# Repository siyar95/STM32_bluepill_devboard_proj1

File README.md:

# STM32 Dev Board – Project 1

This project is a custom **development board** designed around the **STM32F103C8T6** microcontroller.  
It includes the essential peripherals for firmware development and prototyping:

## 🔧 Features

- **STM32F103C8T6** ARM Cortex-M3 microcontroller
- **USB (Device/Power)**
- **UART** interface for serial communication
- **SWD (Single Wire Debug)** header for programming and debugging
- **Linear voltage regulator** for stable 3.3V power supply

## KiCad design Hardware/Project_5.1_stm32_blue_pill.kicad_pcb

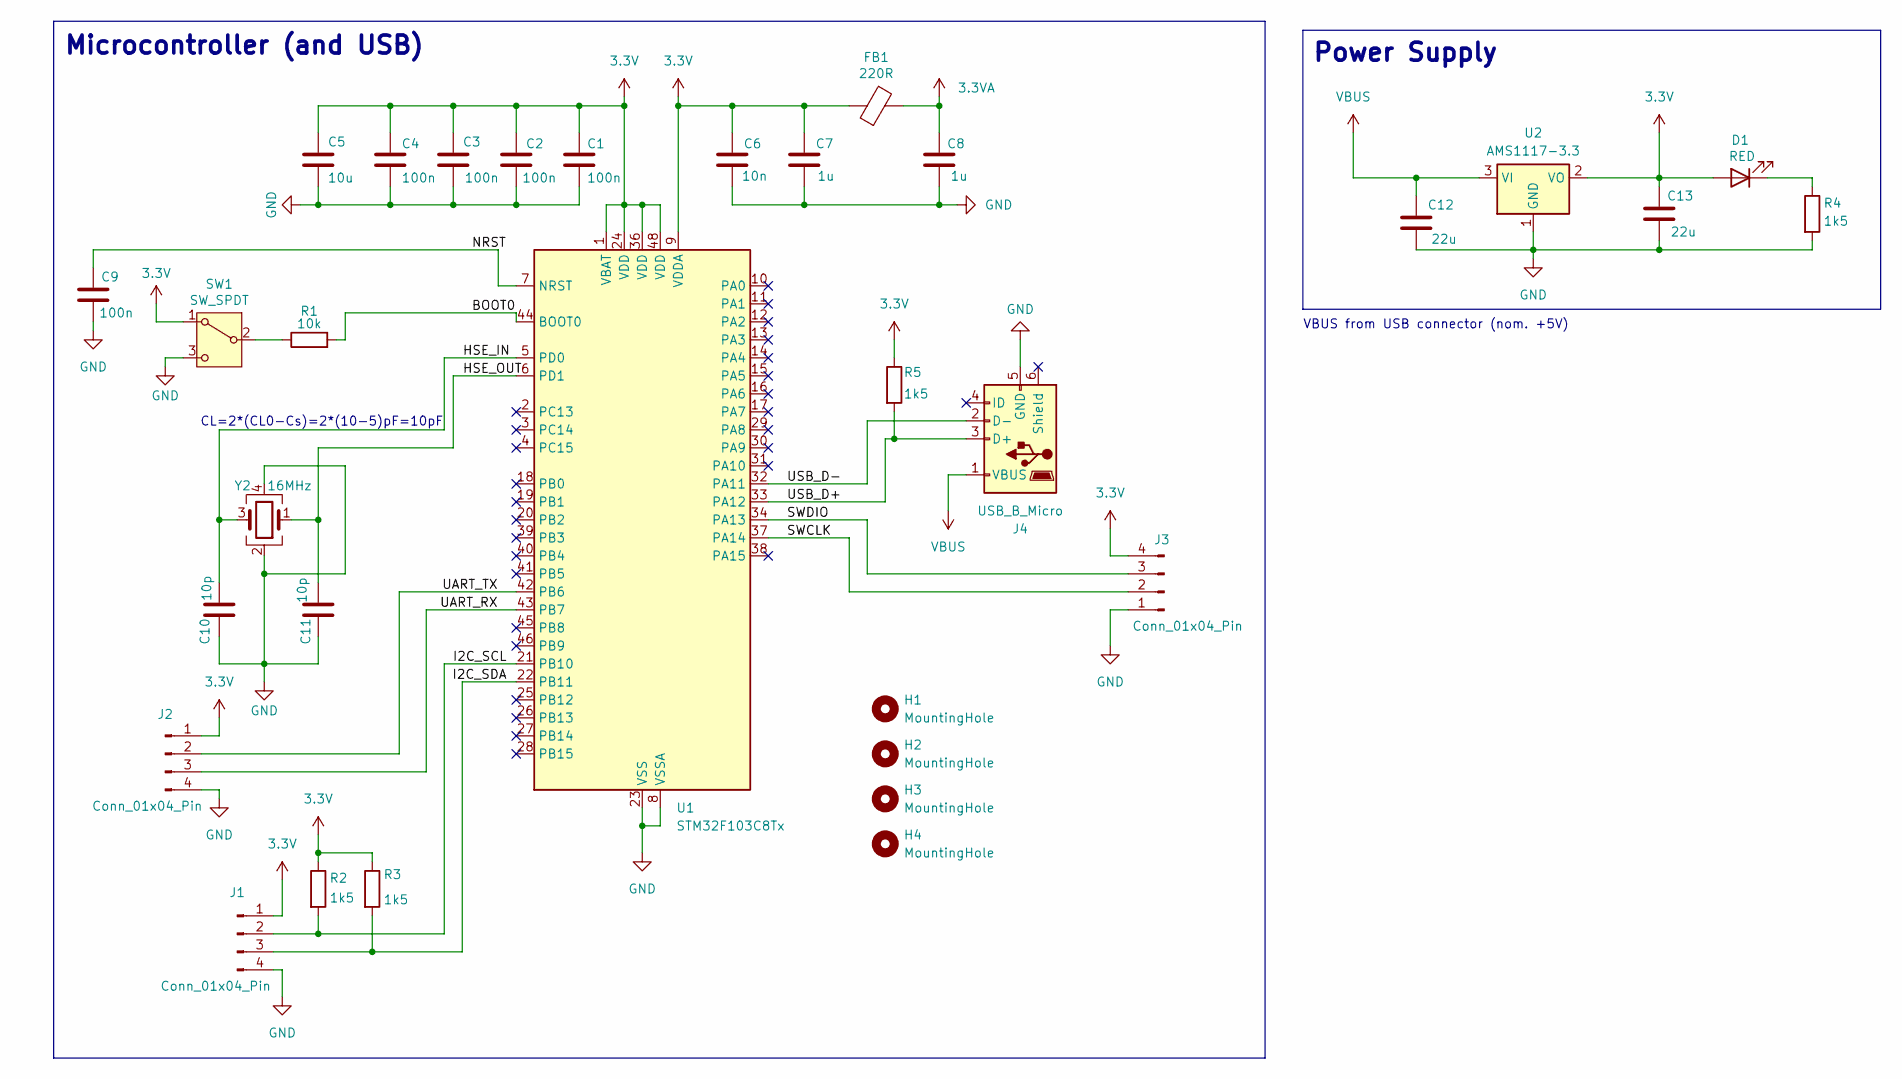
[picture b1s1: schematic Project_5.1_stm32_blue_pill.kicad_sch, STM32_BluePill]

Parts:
C1, C2, C3, C4, C9: 100n; C_0402_1005Metric
C5: 10u; C_0603_1608Metric
C6: 10n; C_0402_1005Metric
C7, C8: 1u; C_0402_1005Metric
C10, C11: 10p; C_0402_1005Metric
C12, C13: 22u; C_0805_2012Metric
D1: RED; LED_0603_1608Metric
FB1: 220R; L_0603_1608Metric
H1, H2, H3, H4: MountingHole; MountingHole_2.2mm_M2
J1, J2, J3: Conn_01x04_Pin; PinHeader_1x04_P2.54mm_Vertical
J4: USB_B_Micro; USB_Micro-B_Wuerth_629105150521
R1: 10k; R_0402_1005Metric
R2, R3, R4, R5: 1k5; R_0402_1005Metric
SW1: SW_SPDT; SW_SPDT_PCM12
U1: STM32F103C8Tx; LQFP-48_7x7mm_P0.5mm
U2: AMS1117-3.3; SOT-223-3_TabPin2
Y2: 16MHz; Crystal_SMD_Abracon_ABM8G-4Pin_3.2x2.5mm

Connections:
3.3V: C1.1, C2.1, C3.1, C4.1, C5.1, C6.1, C7.1, C13.1, D1.2 (A), FB1.1, J1.1, J2.1, J3.4, R2.1, R3.1, R5.1, SW1.1 (A), U1.1 (VBAT), U1.9 (VDDA), U1.24 (VDD), U1.36 (VDD), U1.48 (VDD), U2.2 (VO)
3.3VA: C8.1, FB1.2
/BOOT0: R1.2, U1.44 (BOOT0)
/HSE_IN: C10.2, U1.5 (PD0), Y2.3
/HSE_OUT: C11.2, U1.6 (PD1), Y2.1
/I2C_SCL: J1.2, R2.2, U1.21 (PB10)
/I2C_SDA: J1.3, R3.2, U1.22 (PB11)
/NRST: C9.1, U1.7 (NRST)
/SWCLK: J3.2, U1.37 (PA14)
/SWDIO: J3.3, U1.34 (PA13)
/UART_RX: J2.3, U1.43 (PB7)
/UART_TX: J2.2, U1.42 (PB6)
/USB_D+: J4.3 (D+), R5.2, U1.33 (PA12)
/USB_D-: J4.2 (D-), U1.32 (PA11)
GND: C1.2, C2.2, C3.2, C4.2, C5.2, C6.2, C7.2, C8.2, C9.2, C10.1, C11.1, C12.2, C13.2, J1.4, J2.4, J3.1, J4.5 (GND), R4.2, SW1.3 (C), U1.8 (VSSA), U1.23 (VSS), U1.35 (VSS), U1.47 (VSS), U2.1 (GND), Y2.2, Y2.4
unnamed: D1.1 (K), R4.1
unnamed: R1.1, SW1.2 (B)
VBUS: C12.1, J4.1 (VBUS), U2.3 (VI)

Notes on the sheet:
CL=2*(CL0-Cs)=2*(10-5)pF=10pF
Microcontroller (and USB)
Power Supply
VBUS from USB connector (nom. +5V)

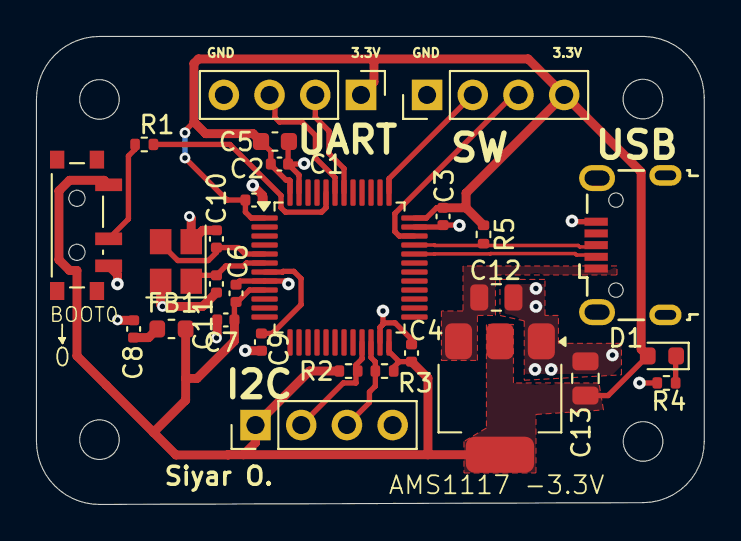
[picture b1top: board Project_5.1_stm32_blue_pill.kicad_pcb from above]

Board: 2 copper layers, 37.1 x 26.0 mm, 32 parts (0 on the bottom side), 18 nets.

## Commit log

2025-05-06 Create Hardware
2025-05-06 Create fe
2025-05-06 Rename Project_5.1_stm32_blue_pill.kicad_pro to Hardware/Project_5.1_stm32_blue_pill.kicad_pro
